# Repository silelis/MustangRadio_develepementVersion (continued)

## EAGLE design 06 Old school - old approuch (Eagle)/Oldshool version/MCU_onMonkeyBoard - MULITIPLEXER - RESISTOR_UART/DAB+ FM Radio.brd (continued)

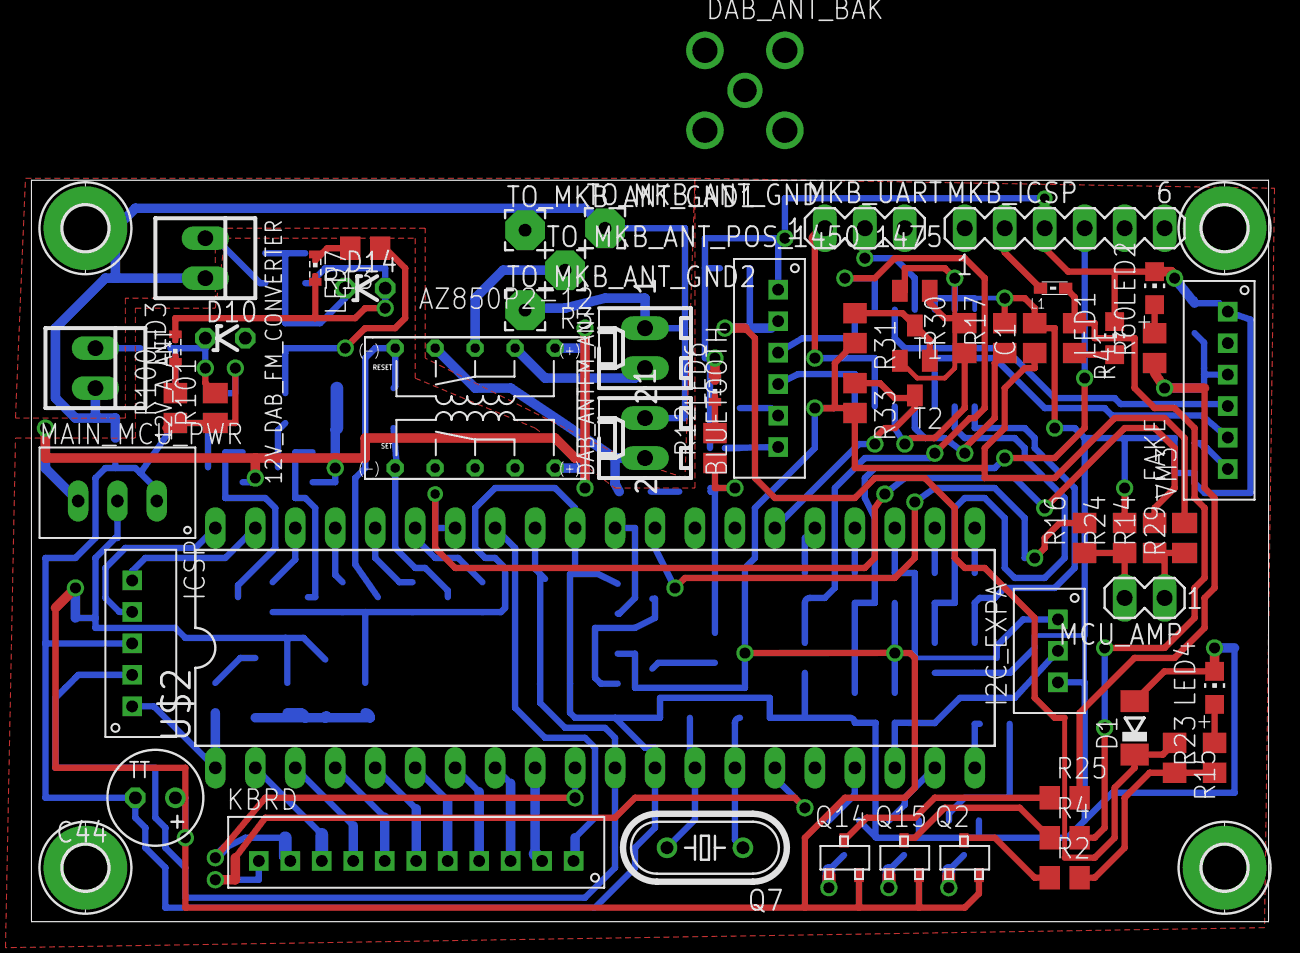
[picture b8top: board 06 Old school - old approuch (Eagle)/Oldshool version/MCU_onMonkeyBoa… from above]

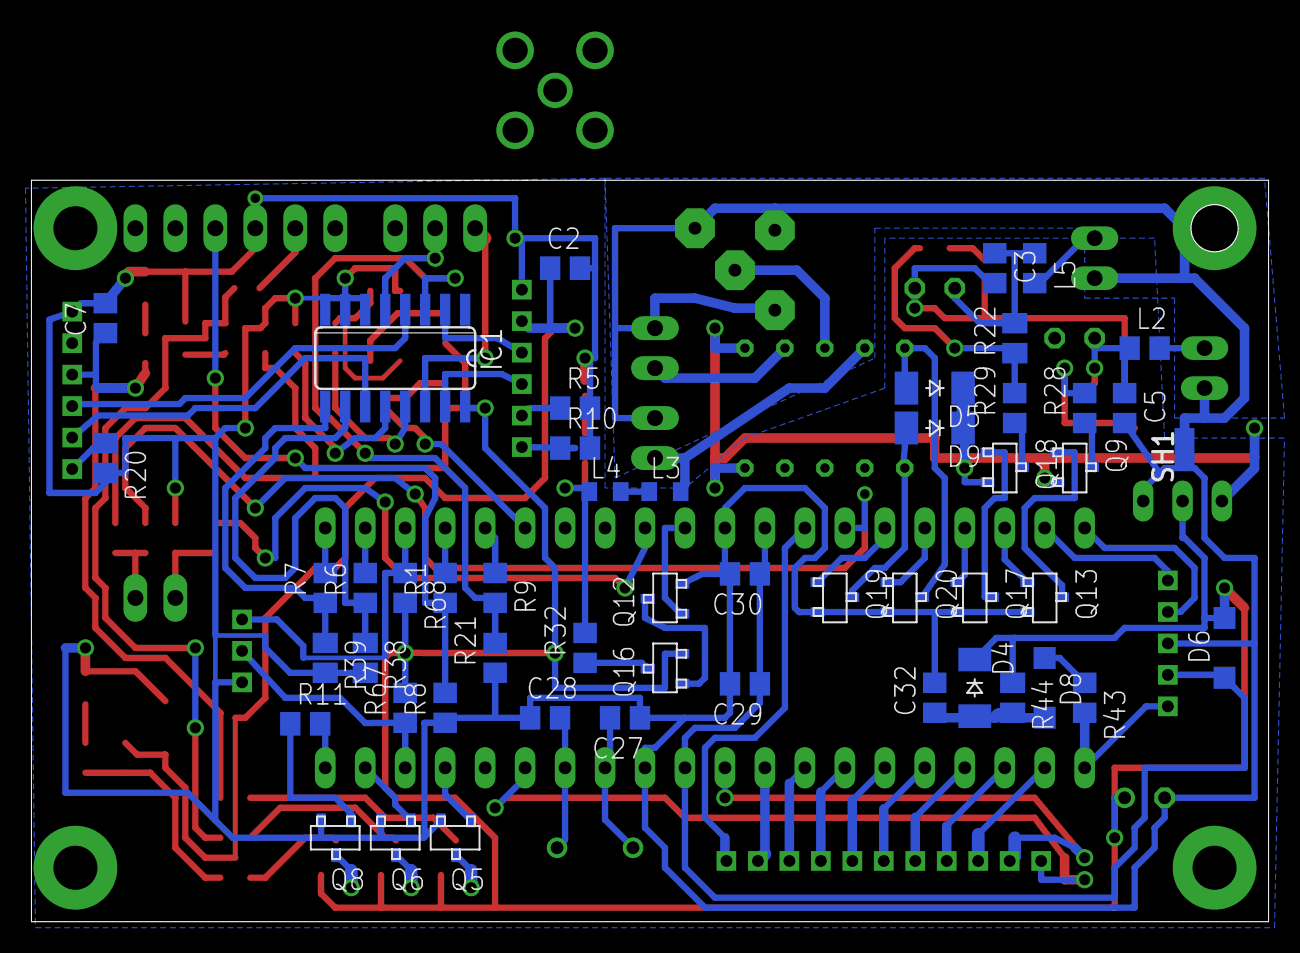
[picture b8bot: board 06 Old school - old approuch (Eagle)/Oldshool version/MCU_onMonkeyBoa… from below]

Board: 2 copper layers, 78.6 x 47.1 mm, 112 parts (51 on the bottom side), 96 nets.

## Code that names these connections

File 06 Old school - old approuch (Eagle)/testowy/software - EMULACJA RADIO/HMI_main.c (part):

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//hardware I2C SLAVE pins - can be changed

//hardware LEDS definition - can be changed
   #define LED1_GREEN   PIN_A0
   #define LED1_RED     PIN_A1   
   #define LED1_BLUE    PIN_A2

   #define LED2_GREEN   PIN_A3
   #define LED2_RED     PIN_A5
   #define LED2_BLUE    PIN_E0
   
   #define LED3_GREEN   PIN_E1
   #define LED3_RED     PIN_E2
   #define LED3_BLUE    PIN_C0
//hardware LEDS definition - can be changed

//Active antena selsctor - can be changed
   #define  IS_FM_ANT_ACTIVE             PIN_B0
   #define  IS_DAB_ANT_ACTIVE            PIN_B1
   #define  IS_FM_DAB_CONVERTER_ACTIVE   PIN_B2
//Active antena selsctor - can be changed

//Steper motor pinout - can be changed
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
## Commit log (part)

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2024-09-08 stm32 esp32 i2c slave
2024-09-12 esp32 i2c slave interrupt - JEST DUŻO DO POPRAWY
2024-09-13 prace nad esp32 i2c receive interrupt - dodano pętlę opóźniającą
2024-09-14 stm32 esp32 prace nad i2c w kopii
2024-09-14 stm32 -fw- commit przed porównaniem plików ioc
2024-09-14 stm32 -fw- HAL_i2c_transmit_dma działa przed wszystkim, potem nie
2024-09-16 stm32 -fw- hal_i2c_master_transmit_DMA buga powoduje xQueueCreate
2024-09-21 stm32 -fw- działa printf jako task, NIE DZIAŁA i2c master transmitt DMA
2024-09-21 stm32 -fw- printfTask wszędzie NIE DZIAŁA i2c master transmit DMA
2024-09-22 prace nad i2c
2024-09-28 esp32 i stm32 -fw- dodano sygnał o zbootowaniu się esp32 i już wiem o co chodzi w i2c_master_transmit_DMA
2024-09-29 stm32 -fw- CRC buf znalexiony - do poprawienia kod (optymalizacja)
2024-09-29 ESP32 bluetooth & HMI -HW- interrupt request pull-down
    Zmieniono R57 - pierwotnie rezystor ten był PULL-UP na linii i2cItterrupt request teraz jest PULL-DOWN
    Zmiana jest po to, aby wykryć start ESp32. Po zboot'owaniu się ESP32 gaje sygnał na tej linii UP
2024-09-30 stm32 -fw- i2c receive z ESP32 działa, sam ESP32 wymaga poprawy stabilności
2024-10-04 stm32 -fw- minor update
2024-10-04 stm32 -fw- działa receive z esp32 po i2c
2024-10-04 ESP32 -fw- poprawiono klawiaturę nie zawiesza się
    zrównałem priorytety taska stepper motora i klawiatury
2024-10-05 esp32 -fw- i2c example adjustment
2024-10-05 ESP32 -fw- działa i2c slave receive callback
2024-10-05 esp32 -fw- dodano opisy funkcji
2024-10-07 ESP32 -fw- coś wiadomo o rx interrupt
2024-10-08 esp32 =fw- I2C0/1 na #define
2024-10-09 esp32 -fw- wpisalem warunke sprawdzania rodzaju przerwania i2c slave
2024-10-11 stm32 -fw- i2c nadawianie tylko teoretycznie
2024-10-13 stm32 / esp32 -fw- dalsze prace nad i2c komunikuje, ale zawiesza
2024-10-13 ESP32 STP32 -fw- komunikacja i2c master transmit działa (SPRAWDZIĆ slave transmit) zrobić porządek
2024-10-14 stm32 -fw- dodano #warning TODO:
2024-10-16 restor Działą klawiatura GOLDEN SAMPLE
2024-10-16 restore point - działą klawiatura GOLDEN SAMPLE2
2024-10-17 stm32 -fw- poprawa w kolejkach i2cQueue4DynamicData - klawiatura działą
2024-10-17 stm32 -fw- poprawa w kolejkach i2cQueue4DynamicData - klawiatura działa GOLDEN BACKUP
2024-10-18 stm32 -fw- czyszczenie kodu KLAWIATURA DZIAŁĄ
2024-10-19 stm32 esp32 -fw- działa albo odbiór albo nadawanie i2c - coś z synchronzacją
2024-10-19 stm32 ESP32-fw- pokombinować z sekwencyjnym przesyłaniem danych
2024-10-20 stm32 -fw- HAL_I2C_Master_Receive_Seq_DMA dodano i klawiatura dziala
    #define ESP32_I2C_Receive_Buffer_LEN UINT8_MAX - dodano
    -do poprawy komunikacja pomiędzy STM32 i ESP32 w jednej ramce za pomocą SEQ
2024-10-20 commom poprawiono size_t /*uint8_t*/ dataSize;
2024-10-22 esp32 -fw- poprawiono metodę esp_err_t i2cEngin_slave::slaveTransmit() - klawiatura działa GOLDEN SAMPLE
    this->interruptRequestSet() jest wyzwalany po zapisaniu bufora nadawczego i2c wszystkimi danymi
2024-10-22 esp32 -fw- update w esp_err_t i2cEngin_slave::slaveTransmit() -klawiatura działa GOLDEN SAMPLE
    this->interruptRequestSet() jest wyzwalany po zapisaniu bufora nadawczego i2c wszystkimi danymi
2024-10-26 GOLDEN SAMPLE - klawiatura działa
2024-10-27 stm32 esp32 -i2c pinpong send-
2024-10-27 transmition true fake
2024-10-27 stm32 (DMA)-> i2c ping -> esp32 - działa
2024-10-27 stm32 (DMA)-> i2c ping -> esp32 - działa BUG FIXED
2024-11-01 i2c ping działa semaphore
2024-11-02 I2C stm32 -> ping ESP32 -> pong -> STM32 - DZIAŁA
2024-11-12 esp32 poprawiono stavleTransmit, ale nie zawiesza się jak nadaje i odbiera
2024-11-16 ESP i STM32 komunikacja po i2c działa NIE DZIAŁA TASK RADIO MENU
2024-11-17 i2c OK GOLDEN SAMPLE
    Zrobić restart jak będzie błąd komunikacji CRC (w STM32) i feed query (w esp32)
2025-04-22 synchronizacja
2025-04-23 punkt przywracania bo zmieniam logike klawiszy
2025-04-24 prace nad klawiaturą
2025-04-26 prace nad klawiatur ą
2025-04-28 trochę dopisane
2025-04-30 działa bindowanie
2025-05-02 dużo poprawione!!!!!
2025-05-03 prace nad obsługą przycisków
2025-05-04 dodano RadioMegaStruct
2025-05-04 wszystkie urządzenia. Trzeba zrobić opisy funkcji i porządek
2025-05-05 praca nad radioMegaStruct
2025-05-07 kilka poprawek
2025-05-08 zmiany w strukturach komunikacji
2025-05-14 praca nad hmiLEDS
2025-05-21 prace nad ledami
2025-05-26 trochę opisów
2025-05-31 praca nad hdmi leds
2025-06-01 transmisja i2c do ESP32 ale zaraz po niej odpowiada głupoty
2025-06-01 i2c transmit from master to esp32 slave znalazłem problem
2025-06-04 prace nad i2c komunikacją
2025-06-08 poprawki związane z backlight
2025-06-08 poprawki w klasie LED
2025-06-09 prace nad kolejką i2cQueue4DynamicData* i2cSlaveReceiveDataToDataParserQueue;
2025-06-12 crc backup point
2025-06-12 CRC - puntk przywracania
    poprawiono błąd w wyliczaniu CRC klawiatury (bylo:
    kbrdDataToI2CSlaveTransmittQueueTemoraryVariable.i2cframeCommandHeader.dataSize = sizeof(keyboardUnion /*keyboardDataToParse*/);
    zamiast poprawnego:
    kbrdDataToI2CSlaveTransmittQueueTemoraryVariable.i2cframeCommandHeader.dataSize = sizeof(i2cFrame_keyboardFrame /*keyboardUnion*/ /*keyboardDataToParse*/);
2025-06-12 komunikacja i2c działa muszę popracować nad - OPIS
    ESP32_SLAVE_RECEIVE_BUFFER_LEN
    i sprawdzić obliczanie CRC
2025-06-13 golden sample przesylanie danych led już działa
2025-06-15 i2c leds komunikacja działa, ale jeszcze sprawdzi c
2025-06-15 GOLDEN SAMPLE - BACKUP
2025-06-16 prace nad stepper motor
2025-06-21 stepper motor poprawnie się porusza - GOLDEN SAMPLE
2025-06-21 dalsze prace nad stepper motor
2025-06-22 funkcje stepper motora zrobione - trzeba przetestowac komunikację i same w sobie funkcje
2025-06-23 poprawiłem wartości w ESP32 resetu emergency i reset to default emergency
2025-07-07 small updte in unions
2025-07-18 stepper motor prace
2025-07-19 stepper komunikaty idą ale kalibracja nie działa
2025-07-22 GOTDLEN BACKUP
2025-07-22 wznawia kalibrację, ale jest gdzieś błąd w disable/enable StepperMotor
2025-07-24 stepper motor - może będzie działac
2025-07-26 stepper - nie działa ponowne wznowienie pracy - np. kalibracji
2025-07-29 robiłem porządki z task functions
2025-07-30 poprawiono taskFunction(s)
2025-09-09 porządek w katalogach firmware
2025-09-20 GURU MEDITATION golden sample
2025-09-20 i2c slave transmitt jesty w tasku, ale dalej jest wdt panic error
2025-09-25 Przed zmianą esp-idf z 5.3.1 na 5.5.1
2025-09-30 nowy GOLDEN SAMPLE powrót do 5.3.1 i w tasku i2c_slave_transmitt
2025-10-01 przejście z VisualGDB na Espressif IDE - ESP-IDF 5.3.1, ale i2c_slave_transmit dalej daje GURU MEDITATION error
2025-10-02 lekkie porządki w howto esp32
2025-10-03 jLink na Espressif IDE dziala
2025-10-03 GDB hardware debugging - skonfigurowane
2025-10-06 GOLDEN BUCKUP przed zmianami w i2c
2025-10-10 errata dot. rezystora R57 i bootowania
2025-10-22 gerbery esp32 jtag hat
2025-10-27 małe poprawki w projekcie HMI
2025-10-29 prace nad uruchomieniem vs code
2025-10-31 kolejne prace nad degubberem w vs code
    - zostło jeszcze otwieranie opengdb przed debuggowaniem i kompilacja programu przed debuggowaniem.
2025-11-01 vs code kolejne prace, ale jak krew w piach
2025-11-02 porządki w repo firmware ESP32 i vs code config final
2025-11-03 Update LICENSE
2025-11-04 dodano ESP32 guru meditation decoder napisany w python i działającey jako task VS CODE
2025-11-05 VS CODE działa - 5.5.1 - GOLDEN SAMPLE przed porządkami
    Dla ESP32:
    - działa VS CODE i2c slave
    - porządki w i2c engine - podzielono na master i slave
2025-11-05 ESP32 - porządek w firmware (tylko VS CODE) i na PCB )dodano złącza ESP PROG)
2025-11-06 Dodano .gitignore - ignorowanie katalogów build
2025-11-06 poprawka błędów gptimer i i2c master - GOLDEN SAMPLE
2025-11-07 backup przed zmianą main.cpp na main.c
2025-11-08 STM32 RadioMain firmware ported to exter "c" - mani.c
2025-11-12 GOLDEN SAMPLE - I2C DMA SEQUENCE restore
2025-11-12 STM32 to ESP32 I2C DMA in sequence NIE DZIAŁA!!! Idź dalej.
2025-11-13 poprawki w keyboardToFunction.h
2025-11-15 prace nas klasą ESP32_a2dp sink
2025-11-17 prace nad bt - moje callbacki nie działają
2025-11-21 vs code json nowe
2025-11-21 prace nat esp32 bt sink
2025-11-22 dalsze prace nad BT
2025-11-22 poprawka
2025-11-22 GOLDEN SAMPLE - przed złączeniem kodu ESP32
2025-11-22 ESP32 a2dp działa - GOLDEN BACKUP
2025-11-23 prace nad bluetooth
2025-11-23 bt audio - po przebojach, ale chyba dobrze
2025-11-30 powinno działać
    - poprawki w nazwach
    - w pętlach while(1){} dodano vTaskDelat(PortmaxDelay); - aby oszczędzać procesowr.
2025-12-01 prace bierzące
2025-12-02 golden sample??
2025-12-02 ledy poprawione i działają
2025-12-03 ESP32 wykasowałem funkcję ping
2025-12-05 GOLDEN BACKUP - przed poprawą przerwania klawiatury
2025-12-05 taki backup, że po dodaniu DRAM_INT działa program, ale błąd występuje
2025-12-09 nie wiem czy to zadziała jest zbuggowana syncgronizacja wysyłania i2c ESP32
2025-12-11 orca slicer config
2025-12-12 taki backup, że po dodaniu DRAM_INT działa program, ale błąd występuje - POWRÓT DO WERSJI
2025-12-13 OrcaSlicer - poprawki
2025-12-16 prace nad sterownikiem i2c V2
2025-12-19 I2C slave v2 - szkic zaczyna działać.
2025-12-30 prace nad poprawką esp32 i2c slave do v2
2026-01-10 Do poprwy jest schemat rotary encodera
2026-02-09 visualGDB działa
2026-02-09 dodano sesje cLion
2026-02-16 dodano opis obsługi jtag w Espressif ide
2026-02-17 ostateczna konfiguracja Espressif IDE openOCD
2026-03-14 dodano ERRATY
2026-03-22 nowa wersja vscode dla esp idf nieprzetestowana
2026-03-26 poprawki w VSCode zrobione przez Clode
2026-03-26 teraz działa
2026-03-28 backup dla błedów cLAUDE cODE
2026-03-29 GOLDEN SAPMLE - powrót do esp-idf5.2 GURU FIXY do wdrożenia i :: zasięg zmiennej lokalnej/globalnej
    -
2026-03-29 Claude code poprawił #ifdefr dla esp-idf >5.2, bo byłyu błedy kompilacji
2026-03-29 poprawka w ESP32-A2dP, bo w ESp-iDF 5.2 nie ma I2S_MCLK_MULTIPLE_192:
2026-03-29 poprawki vs code jason dla esp-idf 5.2 - program nie działa. Trzeba wykasować wszystko co związane z STEPPER motor i2C MAster i MPC (MPS może do stm32 podłaczyć).
2026-03-30 GOLDEN SAMPLE HARDWARE - poprawa bardzo waznej erraty, ktora zabija SMT32!!!!!
2026-03-30 ESP-IDF5.2 GOLDEN SAMPLE
    Są dwie możliwości naprawy (błedu z klawiaturą i i2c):
    1) W ESP-IDF 5.2 - i2c musi transmitować daną dotyczącą wielkości danych a potem przerwanie GPIO i same dane
    2) Migracja do ESP-IDF 5.5.1 i tam stm32 może korzystać z odczytu sekwencyjnego
    3) Nie testowałem czy w esp-idf 5.2 sa się czytać sekwencyjnie. Claude code mowi, ż enei.
2026-04-11 BUCKUP przed poprawkami robionymi przez AI
2026-04-12 CLAUDE poprawki i2c sequence - NIE SPRAWDZONE!!! !!! !!!
